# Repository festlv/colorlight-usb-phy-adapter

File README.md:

USB ULPI phy for Colorlight i5 SOM development board
------------------------------------------------------

Hardware design for dual-PMOD style USB ULPI phy breakout board. 

By default, the design assumes that 24MHz oscillator provides clock to phy, and 60MHz clock generated by PHY is routed to FPGA.
It is possible to supply 24MHz clock from FPGA- see schematic for details.

The design is most likely compatible with several SMSC/Microchip USB phy's from the same series, using different oscillator frequencies (for instance, this board
was first designed for USB3317C, but it went out of stock while the board was designed).

Change history
--------------------

__Revision 0__:

   * VDD1.8 was not connected, as I assumed USB3315C has internal 1.8V regulator. It does not.
   * After bodging a regulator, the design enumerates using LUNA gateware

__Revision 1__:

   * Added 1.8V LDO which was required for the used phy

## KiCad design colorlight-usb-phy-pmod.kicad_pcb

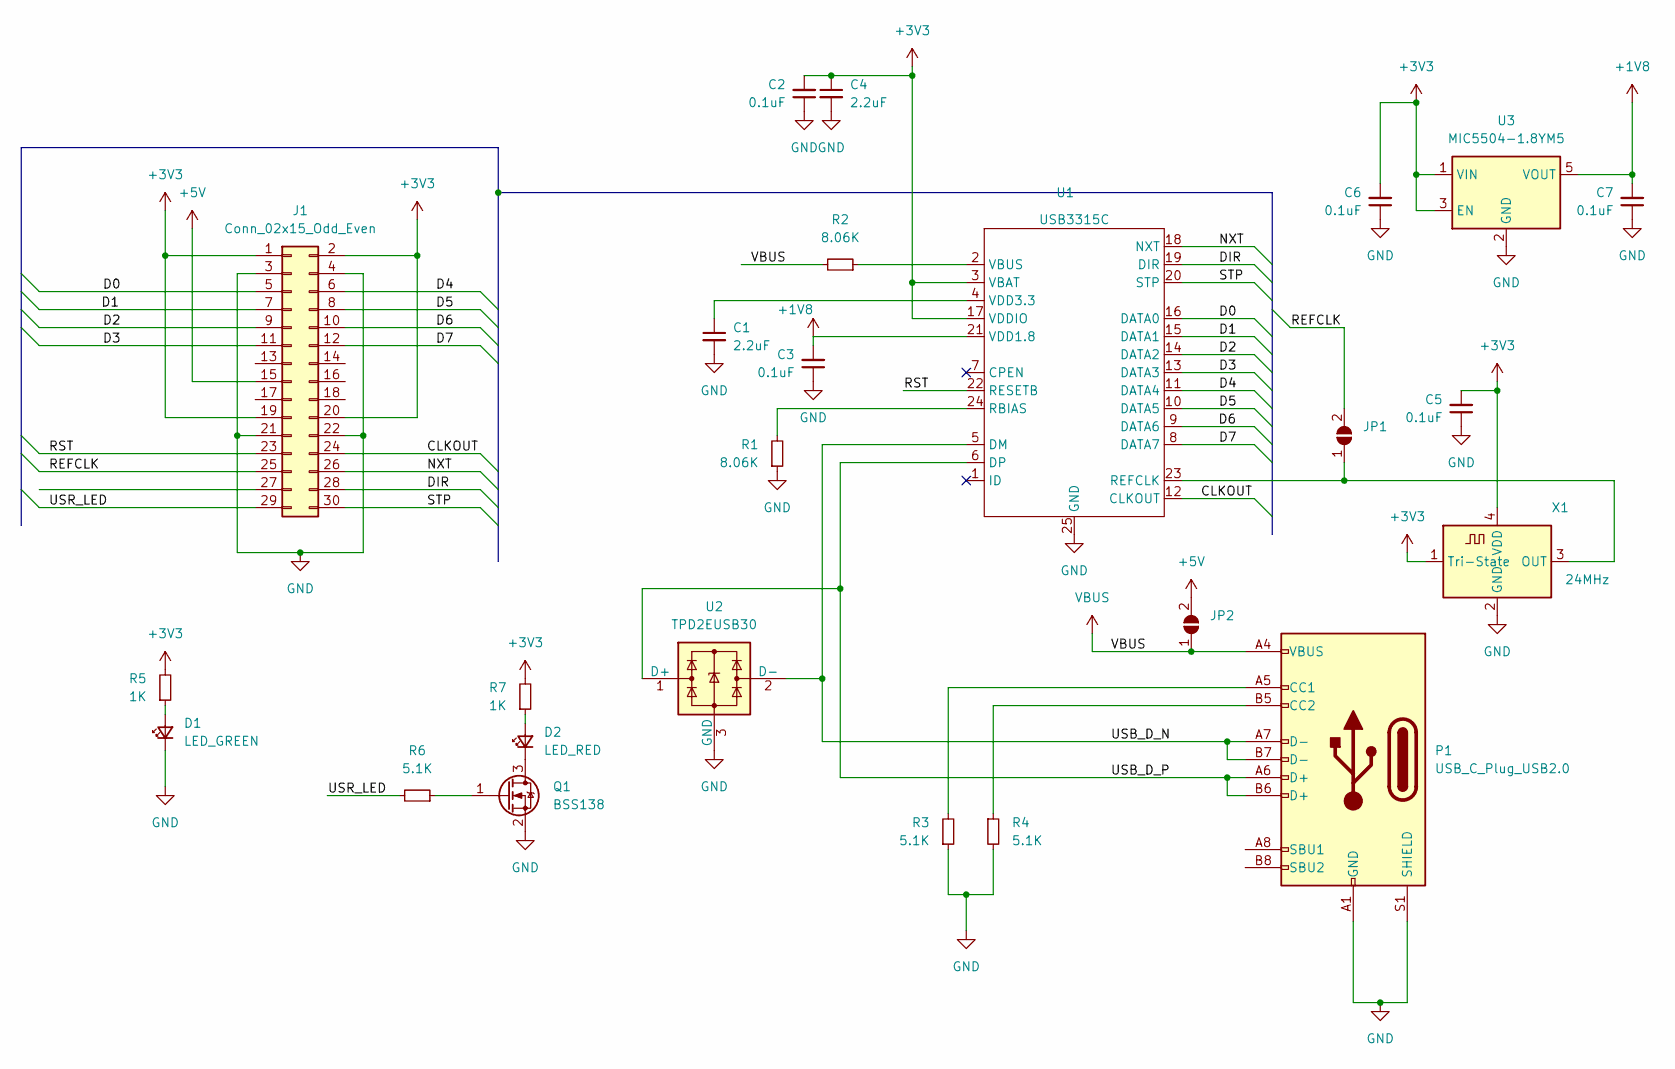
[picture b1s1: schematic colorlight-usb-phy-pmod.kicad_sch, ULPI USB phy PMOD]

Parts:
C1, C4: 2.2uF; C_0402_1005Metric
C2, C3, C5, C6, C7: 0.1uF; C_0402_1005Metric
D1: LED_GREEN; LED_0603_1608Metric
D2: LED_RED; LED_0603_1608Metric
J1: Conn_02x15_Odd_Even; PinHeader_2x15_P2.54mm_Horizontal
JP1, JP2: SolderJumper_2_Open; SolderJumper-2_P1.3mm_Open_TrianglePad1.0x1.5mm
P1: USB_C_Plug_USB2.0; USB_C_Receptacle_HRO_TYPE-C-31-M-12; MPN TYPE-C-31-M-12
Q1: BSS138; SOT-323_SC-70; MPN BSS138PW,115
R1, R2: 8.06K; R_0402_1005Metric
R3, R4, R6: 5.1K; R_0402_1005Metric
R5, R7: 1K; R_0402_1005Metric
U1: USB3315C; QFN-24-1EP_4x4mm_P0.5mm_EP2.6x2.6mm_ThermalVias; MPN USB3315C-CP-TR
U2: TPD2EUSB30; Texas_DRT-3
U3: MIC5504-1.8YM5; SOT-23-5
X1: 24MHz; Oscillator_SMD_ECS_2520MV-xxx-xx-4Pin_2.5x2.0mm; MPN ECS-2520MVLC-240-BN-TR

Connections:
+1V8: C3.2, C7.2, U1.21 (VDD1.8), U3.5 (VOUT)
+3V3: C2.2, C4.1, C5.2, C6.2, J1.1, J1.2, J1.19, J1.20, R5.2, R7.2, U1.3 (VBAT), U1.17 (VDDIO), U3.1 (VIN), U3.3 (EN), X1.1 (Tri-State), X1.4 (VDD)
+5V: J1.15, JP2.2 (B)
/CLKOUT: J1.24, U1.12 (CLKOUT)
/D0: J1.5, U1.16 (DATA0)
/D1: J1.7, U1.15 (DATA1)
/D2: J1.9, U1.14 (DATA2)
/D3: J1.11, U1.13 (DATA3)
/D4: J1.6, U1.11 (DATA4)
/D5: J1.8, U1.10 (DATA5)
/D6: J1.10, U1.9 (DATA6)
/D7: J1.12, U1.8 (DATA7)
/DIR: J1.28, U1.19 (DIR)
/NXT: J1.26, U1.18 (NXT)
/REFCLK: J1.25, JP1.2 (B)
/RST: J1.23, U1.22 (RESETB)
/STP: J1.30, U1.20 (STP)
/USB_D_N: P1.A7 (D-), P1.B7 (D-), U1.5 (DM), U2.2 (D-)
/USB_D_P: P1.A6 (D+), P1.B6 (D+), U1.6 (DP), U2.1 (D+)
/USR_LED: J1.29, R6.2
GND: C1.2, C2.1, C3.1, C4.2, C5.1, C6.1, C7.1, D1.1 (K), J1.3, J1.4, J1.21, J1.22, P1.A1 (GND), P1.A12 (GND), P1.B1 (GND), P1.B12 (GND), P1.S1 (SHIELD), Q1.2 (S), R1.1, R3.1, R4.2, U1.25 (GND), U2.3 (GND), U3.2 (GND), X1.2 (GND)
unnamed: C1.1, U1.4 (VDD3.3)
unnamed: D1.2 (A), R5.1
unnamed: D2.1 (K), Q1.3 (D)
unnamed: D2.2 (A), R7.1
unnamed: JP1.1 (A), U1.23 (REFCLK), X1.3 (OUT)
unnamed: P1.A5 (CC1), R3.2
unnamed: P1.B5 (CC2), R4.1
unnamed: Q1.1 (G), R6.1
unnamed: R1.2, U1.24 (RBIAS)
unnamed: R2.1, U1.2 (VBUS)
VBUS: JP2.1 (A), P1.A4 (VBUS), P1.A9 (VBUS), P1.B4 (VBUS), P1.B9 (VBUS), R2.2

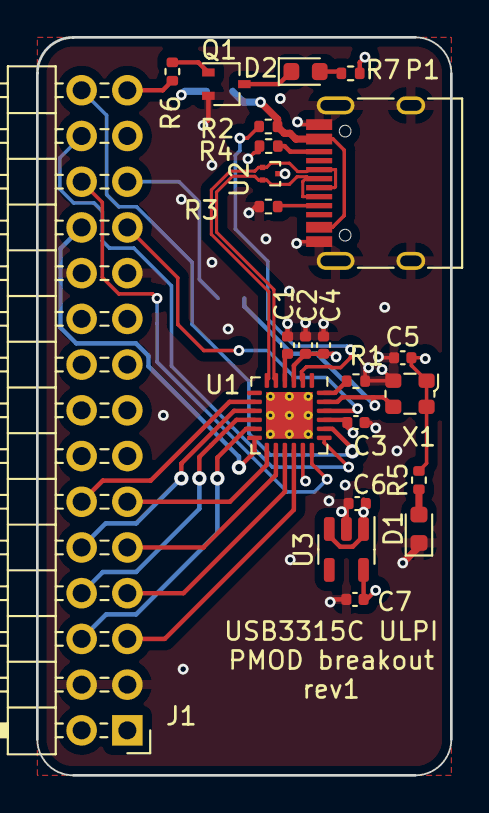
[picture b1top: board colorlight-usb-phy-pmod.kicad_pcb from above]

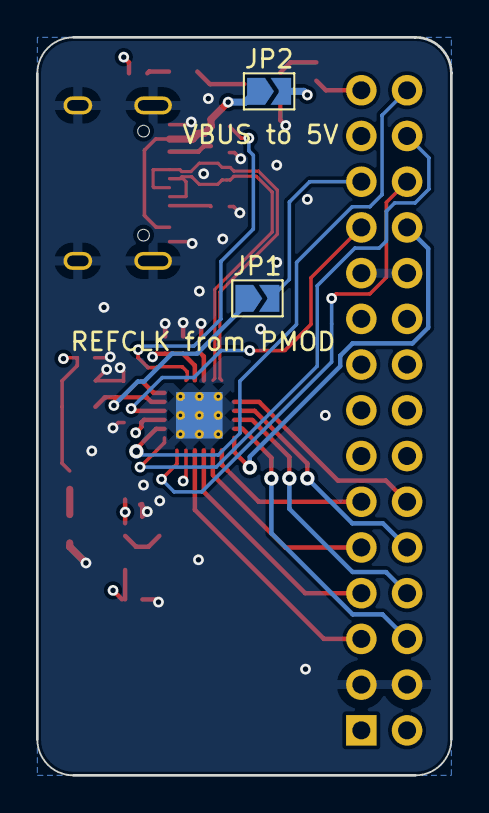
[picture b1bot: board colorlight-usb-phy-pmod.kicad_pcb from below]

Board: 4 copper layers, 23.0 x 41.0 mm, 25 parts (2 on the bottom side), 32 nets.

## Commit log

2022-02-18 Initial commit of rev1 design
